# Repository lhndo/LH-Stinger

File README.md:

<p align="center">
  
	<h1 align="center"><b>LH Stinger</b></h1>
	<p align="center"> <strong>
		A no-compromise cartesian 3D Printer designed for speed and precision, created as a long-lasting platform for those who like to push quality and speed to the extreme.  </strong>
    <br />
    <br />
        <br />
    <i>~ A community-driven project ~ </i>
    <br /> 
    <br />
      
    <br />
</a>
  </p>
</p>

<br>

<br>

Status: **V1.0**  

<br>

## Sponsors

   Sponsored by [JLCPCB Flexible Heaters](https://flexheater.jlcpcb.com/?from=LH_STINGER) - **Custom Flex Heaters for Your Build**
<br>

## Contents

- [Features](#features)
- [Kits - BOM](#kits---bom)
- [Resources](#resources)
- [Assembly Instructions](#assembly-instructions)
- [Addons](#addons)
- [Contact](#contact)
- [Credits](#credits)
- [Supporters](#supporters)
- [License](#license)

<br>

## Features
_**(at BOM Spec)**_
<br>

- Cross Frame design focused on stiffness and stability with a low center of gravity
- Streamlined frame assembly consisting of only six extrusions
- Lightweight bed carriage assembly with carbon fiber components
- AWD stepper configuration for the Y-axis
  - Optional conversion for X-axis AWD setup
- 235 x 235 x 200 mm maximum build volume (easily expandable to other sizes)
  - (200 mm)^2 [Carbon Fiber Bed](/DXF) for high-speed setup
  - (235 mm)^2 bed support for a larger volume
- Optimized for daily print speeds of 400-600 mm/s with 20.000 mm/s^2 acceleration ([Test A](https://www.youtube.com/watch?v=bxNQv3xVFXA&)) ([Test B](https://www.youtube.com/watch?v=mh0rmYptH-0)) ([Test C](https://www.youtube.com/watch?v=cDipS-Msi5c))
- Motion system capable of 1.000 mm/s speed with 100.000 mm/s^2 acceleration ([Test](https://www.youtube.com/watch?v=Xajs2mky6ZU))
- Maximum volumetric flow rate: ~55-60 mm^3/s ([Test A](https://www.youtube.com/watch?v=K3M1EXKJzKs)) ([Test B](https://www.youtube.com/shorts/JorOoNuft90))
- Built using 30 series T-slotted extrusions with parts up to 3090
- All bracket assembly
- Genuine high-quality motion system components ([BOM](https://docs.google.com/spreadsheets/d/1s8ulLfThmbuy1G_40MvkXXL2oVx9PZhvpAY9hMxqYbg/edit?usp=drive_link))
- Entire motion system based on high preload MGN12H linear guide rails
- Fully belt-driven with minimal belt paths
- 9mm 2GT belt in symmetrical configuration for the Y-axis
- 6mm 2GT belts for the rest of the axis
- Independent Z stepper motors with Z Tilt capability for the X-axis
- Lightweight dual plate [Carbon Fiber Bed Carriage](/DXF) with integrated tensioner and compatible with different bed sizes and carriage configurations
- Rigid carbon fiber bed mount
- Lightweight Polyimide flex PCB 200W [Bed Heater](/PCB/PI%20Bed%20Heater%20-%20200mm)
- Double shear shaft supports for Y and X axis steppers
- High torque LDO-42STH48-2504AC stepper motors supplied with 36V for the X and Y-axis
- Dual power supply supporting 24V and 36V power standards (easily configurable for 48V)
- Driven by the Octopus Pro 1.1 board with TMC2240 drivers
- Running [Klipper](https://github.com/Klipper3d/klipper)/[Kalico](https://github.com/KalicoCrew/kalico) firmware
- Fully featured Klipper [Configuration](/Config/Klipper_Config) and [Slicer Profiles](/Config/Klipper_Config#slicers) available
- Easily serviceable [External electronic box](https://github.com/lhndo/LH-Stinger/wiki/Build-Log#electronic-box-design) with good airflow, and support for multiple power supplies, SSRs, RPi and large controller boards.
- Good cable management with a quick disconnect [Breakout Board](/PCB/LHS%20Breakbeat) between the printer and ebox
- Toolhead based on the Dragon HF hotend and HF extender
  - Alternate hotends supported: Dragon UHF, Ace, Mellow NF-Crazy-Volcano HF, Rapido, Goliath ([User Mods](/User_Mods/Toolhead/))
- LDO Orbiter 2.5 direct drive extruder
  - Sherpa Mini supported ([User Mods](/User_Mods/Printer))
- Dual 5015 fan setup for part cooling
- Dual [AUX cooling modules](/CAD/Aux%20Fan) based on 9733 blower fans providing 64 CFM of auxiliary cooling
- Adopts the [Annex Engineering Quickdraw Probe](https://github.com/Annex-Engineering/Quickdraw_Probe)
	- Zero Y offset probe placement for no gantry twist deviation
	- Full bed probe coverage
- Minimalistic [printed part design](/STL) focused on strength and easy printability
- Printed in ASA, providing high temperature resistance
- Easily enclosed, with the main electronic components outside of the build chamber.
  - The (200 mm)^2 bed configuration can be fully enclose up to the frame bounding box, with no extra space needed for the bed movement. ([Dimensions](https://github.com/lhndo/LH-Stinger/wiki/Dimensions))

<br>

**Resonance Tests:**<br>
<br>
<br>

<br>

## Kits - BOM

* This project can be self-sourced by following the [**BOM Guide**](https://docs.google.com/spreadsheets/d/1s8ulLfThmbuy1G_40MvkXXL2oVx9PZhvpAY9hMxqYbg/).  

* An official upgraded **LH Stinger - Rev2 Kit** is produced and sold by **[FYSETC](https://www.fysetc.com/products/lh-stinger-3d-printer-kit)**.

<br>

### Kit Highlights:

* Phaetus Dragon UHF - Hotend
* FYSETC Sherpa Mini - All Metal - CNC Extruder
* MGN 12H Z1 Preload Linear Rails
* FYSETC Spider V3.0 H7 (550Mhz) High Voltage board 
* 48V Power with TMC5160 Drivers (AWD Y, X Axis)
* High Torque 2.5A 580mN.m Stepper Motors with 30mm shafts for double shear support
* Delta (48V) and Meanwell (24V) PSUs
* Carbon Fiber Bed with Pre-applied PI Heater and Pre-epoxied CF Carriage Assembly
* LHS Breakbeat distribution board and wiring harness

**You require**: The **Printed Parts** and a **BTT Pi V1.2** or **Raspberry Pi** SBC (Klipper Host)
<br>

[**Fysetc - LH Stinger - Kit**](https://www.fysetc.com/products/lh-stinger-3d-printer-kit)  
  
Use the code **FYSBKSALELH** for a total of **$699**. Free shipping directly from US/EU.  
A portion of every kit sale goes towards supporting the project! :purple_heart:  

<br>

## Resources
<br>

- [**Assembly Guide**](https://github.com/lhndo/LH-Stinger/wiki/)
- [STL Files and Printing Instructions](STL/)  
- [CAD Source Files ](CAD/)
- [Klipper Configuration ](Config/Klipper_Config) 
- [Build Log](https://github.com/lhndo/LH-Stinger/wiki/Build-Log)
- [Videos](https://www.youtube.com/channel/UCPD2Ai4b49gVoCFSGFWoSdw) 

<br>

## Assembly Instructions 

* The [LH Stinger Wiki](https://github.com/lhndo/LH-Stinger/wiki) is a regularly updated and intended to serve as your primary point of reference during the build  

* The main body of documentation can be found in the [**Assembly Guide**](https://github.com/lhndo/LH-Stinger/wiki/Assembly-Guide)  

<br>

*For additional support please join us on the [LH Stinger Discord](https://discord.gg/EzssCfnEDS)*

<br>

## Addons

- [**LHS Pico MMU**](https://github.com/lhndo/LH-Stinger/wiki/Pico-MMU)  

- **Enclosure** *(In progress)* 
  *by zwirbel*

<br>

<br>

- An extensive range of [**community mods**]((/User_Mods)) available

<br>

## Contact

lemurshaze @ gmail.com  
@LH on [LH Stinger Discord](https://discord.gg/EzssCfnEDS)
<br>

## Credits

<br>

**Thanks to everyone in the LH Stinger community who supported the project, contributed in any form, or provided feedback! :purple_heart:**

<br>

_Inspired by the [Annex Engineering](https://github.com/Annex-Engineering) team and [community](https://discord.com/invite/MzTR3zE), along with the [Klipper community](https://discord.klipper3d.org), [RatRig](https://ratrig.com/) and all the crazy people that continue to push bed slingers to their limits. :purple_heart:_

-Toolhead evolved from an amazing design by [Dalegaard](https://github.com/dalegaard)  
-Silicon sock mold based on [Renátó Kulman](https://www.printables.com/@RenatoKulman)  
-Wago 221 mounts by [fns720](https://www.printables.com/@fns720)  
-SSR protection cover based on [Technoturk](https://www.printables.com/@Technoturk_377911)  
-3030 extrusion Cable clip based on [Arthur_C](https://www.printables.com/@Arthur_C_428094)  
-3030 t-nut clip based on [John_S](https://www.printables.com/@JohnS)  
<br>

## Supporters

<br>

*Special thanks to those who donated to this project throughout its development!* :purple_heart:  

**djezo888. Fen, Budz, techb0i, PinGZ, abstractFlo, BeccaK, Steven @crydteam, Robin @crydteam, Fred Bernton, Mawoka, rmxbit, Mcclane, malar6606, EMMY BEAR 3D, Killa_Prints, Michel, vr6deezy, Ajax240, Zemlos01, popster, Dan, Sibert, Ultracopa, yoske, Arjun, iKuro**  

If you would like to give your support, please use the link below:

<br>

## License

This work is licensed under a [Creative Commons (4.0 International License)  ](https://creativecommons.org/licenses/by-nc-sa/4.0/)  
[**Attribution—Noncommercial—Share Alike**](LICENSE.md)  

[![CC BY-NC-SA 4.0][cc-by-nc-sa-shield]][cc-by-nc-sa] [![DISCORD][s2]][l2] [![YOUTUBE][s5]][l5] 

[s1]: https://img.shields.io/badge/Buy%20Me%20a%20Coffeee-d3dsds?logo=ko-fi&logoColor=white&labelColor=red&color=red
[l1]: https://ko-fi.com/lh_eng
[s2]: https://img.shields.io/badge/Discord-asdsadsa?logo=discord&logoColor=white&color=5865F2
[l2]: https://discord.gg/EzssCfnEDS
[s5]: https://img.shields.io/badge/Youtube-8A2323443?logo=youtube&logoColor=red&color=white
[l5]: https://www.youtube.com/@LemurHaze

[cc-by-nc-sa]: http://creativecommons.org/licenses/by-nc-sa/4.0/
[cc-by-nc-sa-image]: https://licensebuttons.net/l/by-nc-sa/4.0/88x31.png
[cc-by-nc-sa-shield]: https://img.shields.io/badge/License-CC%20BY--NC--SA%204.0-lightgrey.svg

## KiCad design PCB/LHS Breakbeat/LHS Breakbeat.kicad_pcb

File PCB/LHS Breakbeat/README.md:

# LHS Breakbeat

- [LHS Breakbeat](#lhs-breakbeat)
  - [Features](#features)
  - [Specifications](#specifications)
  - [BOM](#bom)
  - [Notes](#notes)
- [Wiring Harness](#wiring-harness)
- [Guide](#guide)
- [Acknowledgments](#acknowledgments)

<br>

**Disclaimer**

>*This is a DIY (Do-It-Yourself) experimental project. This PCB is provided "as is" without any guarantees or warranty, and is not certified for any commercial or critical applications. Use it at your own risk. 
The creator assumes no liability for damages or injuries resulting from its use, including but not limited to fire, electric shock, personal injury or property damage.*
>*By using this PCB, you agree to the terms of this disclaimer.*

<br>

**NOTE: this design is currently in testing**  

<br>

**LHS Breakbeat** is a breakout board built for the LH Stinger, meant to provide an easy interface between the external electronics box and the printer electronics.

This board is meant to be mounted on the printer, and make most of the wiring setup plug and play.

## Features
* Support for 7 stepper motors
* 3 Thermistors
* 3 Fans with individual power requirements
  * 4-pin fan support
* 4 Endstops
* RGB lighting
* Optional probe header
* Filament Sensor (Tach and F Sens pins are shared)
* Fused bed and hotend power lines 
* Support for separate thermistor analog ground
* CAN bus alternative wiring
* Thermistor test points
* Tachometer diode protection

<br>

## Specifications

Note: these guideline limits are on top of your mainboard specifications, along with the wires and connectors used for the wire harness.

Circuit | Limit
--|--
Hotend Heater | 24V, 115W, 4.8 A 
Bed Heater | 24V, 220W, 9.2 A
Fans | 24V, 2 A 
RGB/5V | 2A
Steppers | 2.7 A

## BOM
Please see the [Interactive BOM](https://htmlpreview.github.io/?https://github.com/lhndo/LH-Stinger/blob/main/PCB/LHS%20Breakbeat/BOM/ibom.html)

## Notes

* The BOM included links to paired connectors and crimps
* The Molex MiniFit Paired Power Connector (03-04-4052) requires 16AWG 13A crimps (45750-3112)

<br>

# Wiring Harness

<br>

# Guide

https://github.com/lhndo/LH-Stinger/wiki/Breakout-Box

# Acknowledgments

*Thanks to [@roerich_64](https://github.com/walterwissmann) and the LHS community for the help and guidance with this project!*

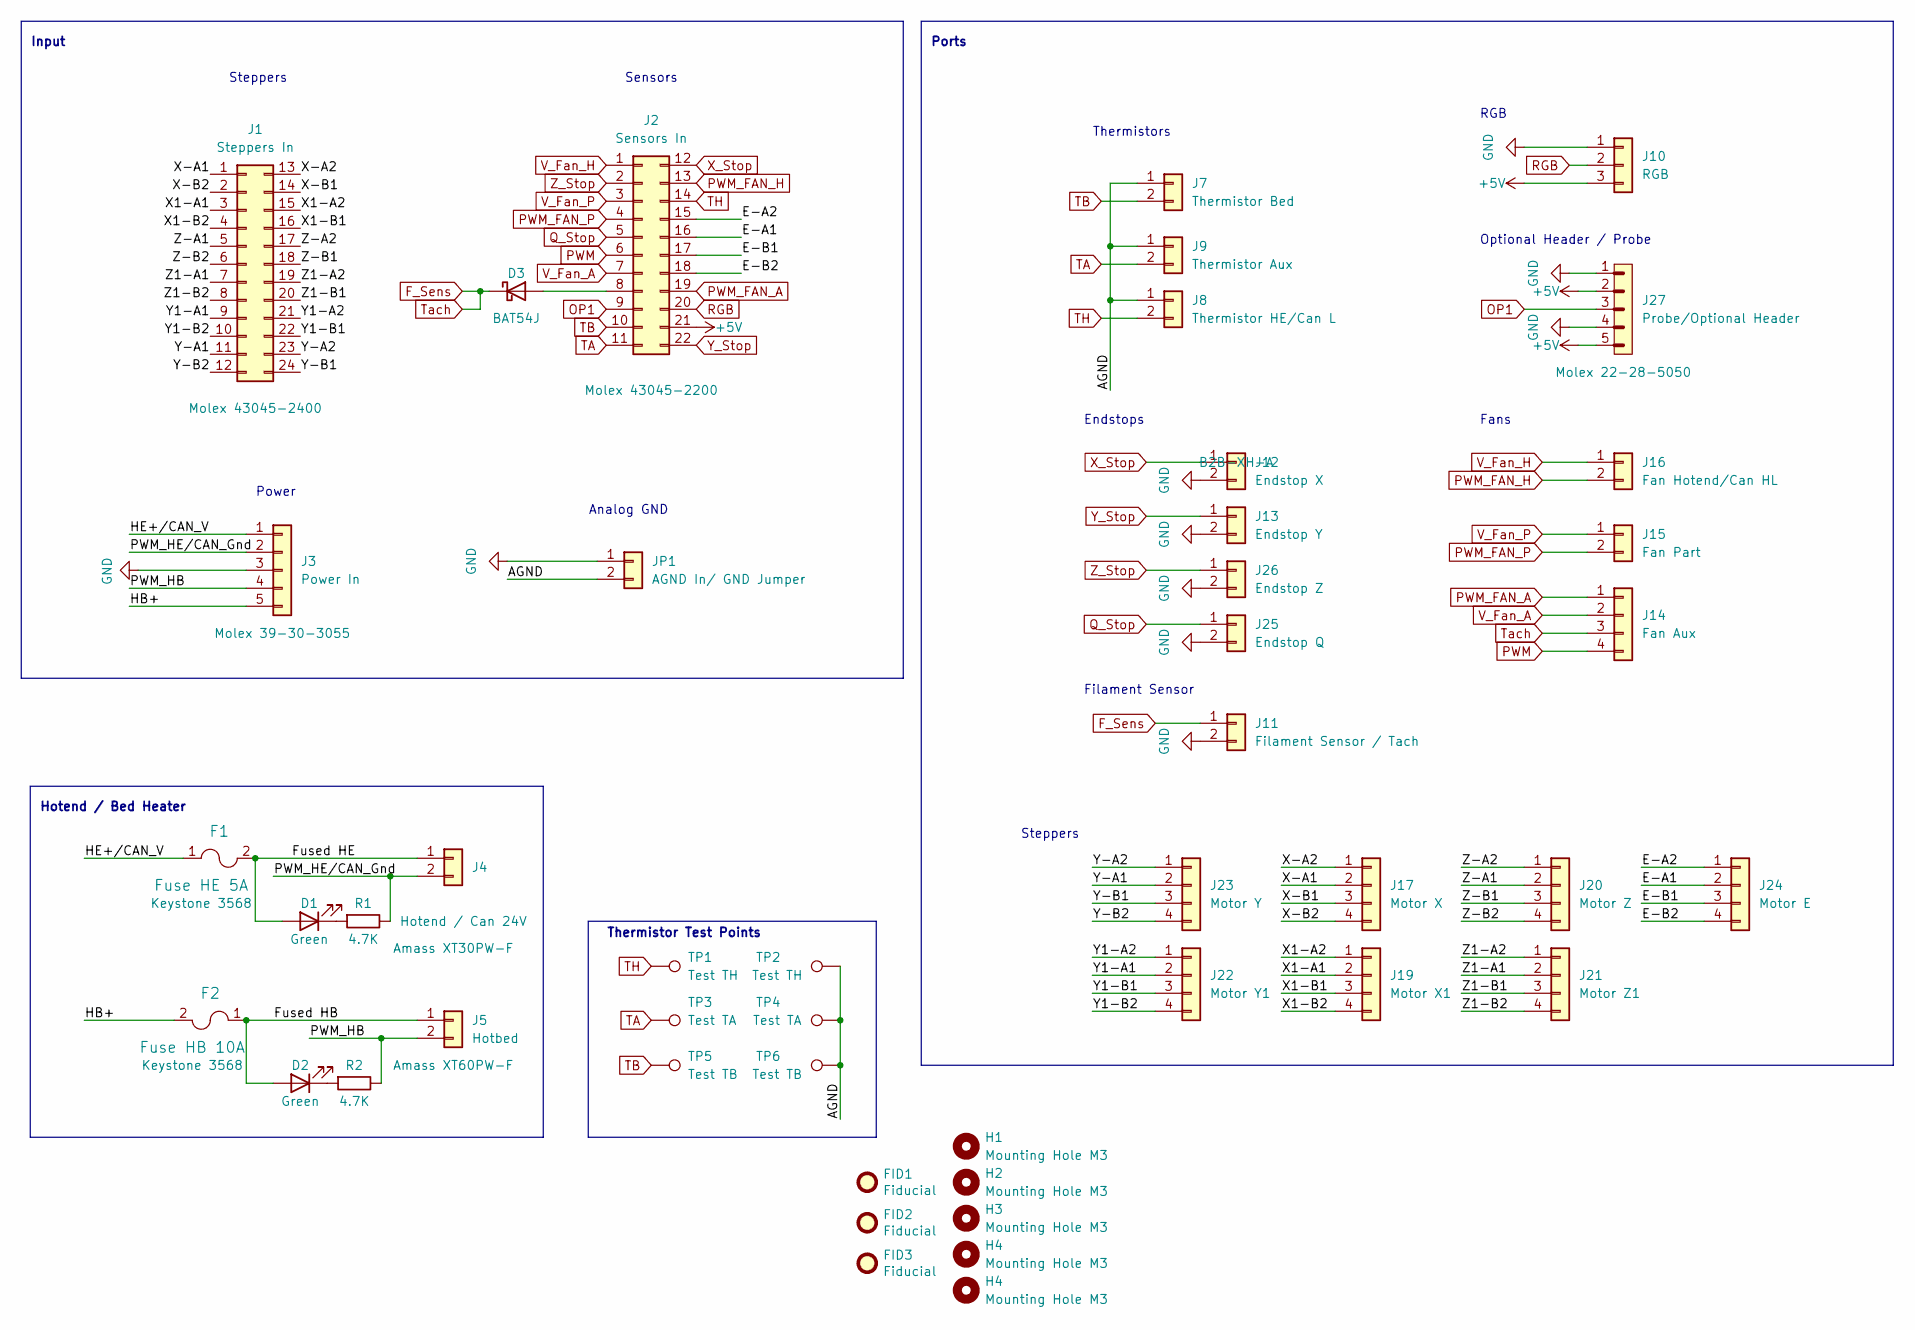
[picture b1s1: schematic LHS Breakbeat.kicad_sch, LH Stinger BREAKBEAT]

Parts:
D1, D2: Green; LED_0805_2012Metric_Pad1.15x1.40mm_HandSolder; LCSC C2297
D3: BAT54J; D_SOD-323F; LCSC C130415
F1: Fuse HE 5A; Fuseholder_Blade_Mini_Keystone_3568; LCSC C3206956
F2: Fuse HB 10A; Fuseholder_Blade_Mini_Keystone_3568; LCSC C3206956
FID1, FID2, FID3: Fiducial; Fiducial_1.5mm_Mask3mm
H1, H2, H3, H4: Mounting Hole M3; MountingHole_3.2mm_M3_DIN965_Pad
J1: Steppers In; 0430452400; LCSC C277384
J2: Sensors In; 43045-22_00,01,02,10_; LCSC C127339
J3: Power In; 39303055; LCSC C485326
J4: Hotend / Can 24V; XT30PWF; LCSC C2913282
J5: Hotbed; AMASS_XT60PW-F_1x02_P7.20mm_Horizontal; LCSC C428722
J7: Thermistor Bed; JST_XH_B2B-XH-A_1x02_P2.50mm_Vertical; LCSC C5258883
J8: Thermistor HE/Can L; JST_XH_B2B-XH-A_1x02_P2.50mm_Vertical; LCSC C5258883
J9: Thermistor Aux; JST_XH_B2B-XH-A_1x02_P2.50mm_Vertical; LCSC C5258883
J10: RGB; JST_XH_B3B-XH-A_1x03_P2.50mm_Vertical; LCSC C492457
J11: Filament Sensor / Tach; JST_XH_B2B-XH-A_1x02_P2.50mm_Vertical; LCSC C5258883
J12: Endstop X; JST_XH_B2B-XH-A_1x02_P2.50mm_Vertical; LCSC C5258883
J13: Endstop Y; JST_XH_B2B-XH-A_1x02_P2.50mm_Vertical; LCSC C5258883
J14: Fan Aux; JST_XH_B4B-XH-A_1x04_P2.50mm_Vertical; LCSC C709375
J15: Fan Part; JST_XH_B2B-XH-A_1x02_P2.50mm_Vertical; LCSC C5258883
J16: Fan Hotend/Can HL; JST_XH_B2B-XH-A_1x02_P2.50mm_Vertical; LCSC C5258883
J17: Motor X; JST_XH_B4B-XH-A_1x04_P2.50mm_Vertical; LCSC C709375
J19: Motor X1; JST_XH_B4B-XH-A_1x04_P2.50mm_Vertical; LCSC C709375
J20: Motor Z; JST_XH_B4B-XH-A_1x04_P2.50mm_Vertical; LCSC C709375
J21: Motor Z1; JST_XH_B4B-XH-A_1x04_P2.50mm_Vertical; LCSC C709375
J22: Motor Y1; JST_XH_B4B-XH-A_1x04_P2.50mm_Vertical; LCSC C709375
J23: Motor Y; JST_XH_B4B-XH-A_1x04_P2.50mm_Vertical; LCSC C709375
J24: Motor E; JST_XH_B4B-XH-A_1x04_P2.50mm_Vertical; LCSC C709375
J25: Endstop Q; JST_XH_B2B-XH-A_1x02_P2.50mm_Vertical; LCSC C5258883
J26: Endstop Z; JST_XH_B2B-XH-A_1x02_P2.50mm_Vertical; LCSC C5258883
J27: Probe/Optional Header; PinHeader_1x05_P2.54mm_Vertical; LCSC C2935911
JP1: AGND In/ GND Jumper; PinHeader_1x02_P2.54mm_Vertical; LCSC C2685195
R1, R2: 4.7K; R_0805_2012Metric_Pad1.20x1.40mm_HandSolder; LCSC C17673
TP1, TP2: Test TH; TestPoint_Pad_D2.0mm
TP3, TP4: Test TA; TestPoint_Pad_D2.0mm
TP5, TP6: Test TB; TestPoint_Pad_D2.0mm

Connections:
+5V: J2.21, J10.3, J27.2, J27.5
/AGND: J7.1, J8.1, J9.1, JP1.2, TP2.1, TP4.1, TP6.1
/E-A1: J2.16, J24.2
/E-A2: J2.15, J24.1
/E-B1: J2.17, J24.3
/E-B2: J2.18, J24.4
/Fused HB: D2.2 (A), F2.1, J5.1
/Fused HE: D1.2 (A), F1.2, J4.1
/HB+: F2.2, J3.5
/HE+/CAN_V: F1.1, J3.1
/PWM_HB: J3.4, J5.2, R2.2
/PWM_HE/CAN_Gnd: J3.2, J4.2, R1.2
/X1-A1: J1.3, J19.2
/X1-A2: J1.15, J19.1
/X1-B1: J1.16, J19.3
/X1-B2: J1.4, J19.4
/X-A1: J1.1, J17.2
/X-A2: J1.13, J17.1
/X-B1: J1.14, J17.3
/X-B2: J1.2, J17.4
/Y1-A1: J1.9, J22.2
/Y1-A2: J1.21, J22.1
/Y1-B1: J1.22, J22.3
/Y1-B2: J1.10, J22.4
/Y-A1: J1.11, J23.2
/Y-A2: J1.23, J23.1
/Y-B1: J1.24, J23.3
/Y-B2: J1.12, J23.4
/Z1-A1: J1.7, J21.2
/Z1-A2: J1.19, J21.1
/Z1-B1: J1.20, J21.3
/Z1-B2: J1.8, J21.4
/Z-A1: J1.5, J20.2
/Z-A2: J1.17, J20.1
/Z-B1: J1.18, J20.3
/Z-B2: J1.6, J20.4
F_Sens: D3.1 (K), J11.1, J14.3
GND: J3.3, J10.1, J11.2, J12.2, J13.2, J25.2, J26.2, J27.1, J27.4, JP1.1
unnamed: D1.1 (K), R1.1
unnamed: D2.1 (K), R2.1
unnamed: D3.2 (A), J2.8
OP1: J2.9, J27.3
PWM: J2.6, J14.4
PWM_FAN_A: J2.19, J14.1
PWM_FAN_H: J2.13, J16.2
PWM_FAN_P: J2.4, J15.2
Q_Stop: J2.5, J25.1
RGB: J2.20, J10.2
TA: J2.11, J9.2, TP3.1
TB: J2.10, J7.2, TP5.1
TH: J2.14, J8.2, TP1.1
V_Fan_A: J2.7, J14.2
V_Fan_H: J2.1, J16.1
V_Fan_P: J2.3, J15.1
X_Stop: J2.12, J12.1
Y_Stop: J2.22, J13.1
Z_Stop: J2.2, J26.1

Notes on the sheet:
Fans
Analog GND
Power
Endstops
Input
Hotend / Bed Heater
Steppers
Ports
Thermistors
Optional Header / Probe
Filament Sensor
Thermistor Test Points
Sensors
RGB

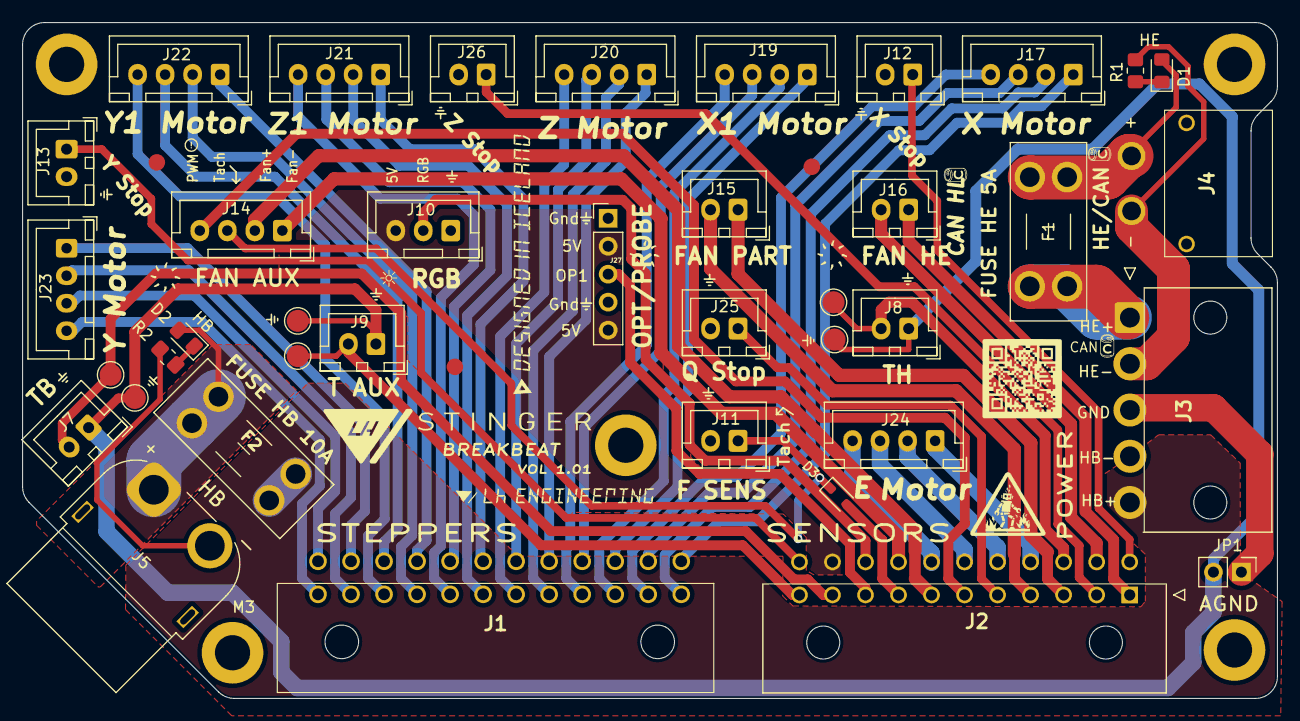
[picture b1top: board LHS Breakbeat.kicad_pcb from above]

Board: 2 copper layers, 114.0 x 61.4 mm, 47 parts (0 on the bottom side), 57 nets.

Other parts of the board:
H5: Mounting Hole M3; MountingHole_3.2mm_M3_DIN965_Pad

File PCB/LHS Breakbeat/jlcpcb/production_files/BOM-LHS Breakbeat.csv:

Comment,Designator,Footprint,LCSC
Sensors In,J2,"43045-22_00,01,02,10_",C127339
BAT54J,D3,D_SOD-323F,C130415
4.7K,"R1,R2",R_0805_2012Metric_Pad1.20x1.40mm_HandSolder,C17673
Green,"D1,D2",LED_0805_2012Metric_Pad1.15x1.40mm_HandSolder,C2297
AGND In/ GND Jumper,JP1,PinHeader_1x02_P2.54mm_Vertical,C2685195
Steppers In,J1,0430452400,C277384
Hotend / Can 24V,J4,XT30PWF,C2913282
Probe/Optional Header,J27,PinHeader_1x05_P2.54mm_Vertical,C2935911
Fuse HE 5A,"F1,F2",Fuseholder_Blade_Mini_Keystone_3568,C3206956
Hotbed,J5,AMASS_XT60PW-F_1x02_P7.20mm_Horizontal,C428722
Power In,J3,39303055,C492364
RGB,J10,JST_XH_B3B-XH-A_1x03_P2.50mm_Vertical,C492457
Filament Sensor / Tach,"J11,J12,J13,J15,J16,J25,J26,J7,J8,J9",JST_XH_B2B-XH-A_1x02_P2.50mm_Vertical,C5258883
Fan Aux,"J14,J17,J19,J20,J21,J22,J23,J24",JST_XH_B4B-XH-A_1x04_P2.50mm_Vertical,C709375

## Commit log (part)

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2024-08-22 explicitly defining extruder speed limits due to possibly wrong klipper default value calculations
2024-08-24 adding fluidd theme
2024-08-25 adding micro cuts to X Endstop to help with bridging layer
2024-08-25 increasing the tolerance of the X Toolhead Tensioner block
2024-08-26 updating zone names
2024-08-30 adding information and linking to the wiki mod guide
2024-09-01 decreasing bottom part thickness to increase clearance against Y extrusion
2024-09-02 updating setup instruction
2024-09-02 updating bed PID and sensor values
2024-09-04 updating hz_per_sec to speed up testing
2024-09-04 adding a custom TPOWERDOWN setting of ~4.3 seconds along with 1A hold current for the HV steppers
2024-09-05 adding max_extrude_cross_section as a safety measure for purges
2024-09-05 enabling [resonance_holder] by default and adding documentation links
2024-09-05 Resonance Holder now part of the main configuration
2024-09-06 improving AWD sync and FORCE_SET_POS to lock at full steps, prefixing NON-UI macros to for exclusion (_PURGE_LINE, _GO_....)
2024-09-09 renaming folder
2024-09-10 updating Z right drive to universal bearing clamp version
2024-09-10 setting speeds for FORCE_UP DOWN macros
2024-09-15 marking the bed heater alignment guide plate as "not for fysetc"
2024-09-15 lowering nozzle pre-heat target to prevent oozing
2024-09-17 updating header FW flashing instructions
2024-09-21 updating formatting
2024-09-21 adding wiring diagram
2024-09-22 adding UL3239 to power wiring specifications
2024-09-25 fixing typo in max_extrude_cross value
2024-09-25 changing 5160 stepper drivers to hardware spi
2024-09-29 adding TPU profiles
2024-10-03 print start: adding an extra Z home just before docking
2024-10-08 adding Stinger Pico MU - prototype
2024-10-09 Updating UL codes
2024-10-09 updating BOM
2024-10-11 adding Pico MMU step file
2024-10-15 Pico MMU: adding optional ECAS fittings
2024-10-16 disabling my_end_retract moves if the value is set to 0
2024-10-20 adding other parts - accesories - for the Pico MMU
2024-10-22 integrated cam shaft update
2024-10-22 updating ResHelper instructions and simplifying intallation steps
2024-10-24 taller roller rims and concave profile, adding attachment slot to mid section for future accesories
2024-10-26 adding Pico MMU documentation link
2024-10-27 adding note regarding park at cancel
2024-10-27 adding Stinger Pico MMU Klipper code
2024-10-28 fixed screw quantities
2024-10-28 fixing version check
2024-11-23 Increrasing tolerances of the Cable Clamps
2024-11-27 decreasing tolerances for the X inner tensioner piece for ease of installation
2024-12-02 updated heatbed instructions
2024-12-02 adding other platforms paths
2024-12-03 moving stl files
2024-12-03 adding heat insert for the left fan arm on sherpa variants
2024-12-03 updating UHF toolhead variant for left fan heat insert
2024-12-06 fixing title
2024-12-06 adding download folder link
2024-12-06 added bom links
2024-12-06 renaming Other Parts to Accessories
2024-12-07 removing dock adjustment note
2024-12-07 fixing SP_TEST_MMU
2024-12-07 updating plates image preview
2024-12-07 updating adxl configs for the new sweeping vibrations resonance testing
2024-12-09 fixing end_of_load_filament_move
2024-12-09 adding accel per hz recommendation
2024-12-09 adding restart method to serial connection
2024-12-11 adding 4 lane version
2024-12-11 updating Pico MMU hardware configuration example
2024-12-11 added print plates thumbnail
2024-12-12 adding long shaft link
2024-12-13 adding automatic "Quiet" profile detection part of print start
2024-12-14 setting first layer to rectilinear, adding brim and removing el foot compensation for better overhang fillets
2024-12-15 updating servo link
2024-12-17 updated code and configuration to v0.4 added support for different hub configurations fine tuned movement stages for non ideal setups various other fixes and improvements
2024-12-17 increasing default servo switch time for safety
2024-12-17 adding part variants with higher tolerances - marked with a dot
2024-12-18 adding RatOS T0 conflict workaround
2024-12-19 updating load/unload macros to retain the target heat when ran by default
2024-12-19 tweaking default lengths, bringing synced move closer to sensor and reverting tip forming initial move from 1mm to 0.5mm
2024-12-21 updating Fysetc Spider H7 Mount
2024-12-23 updated print settings and bom
2024-12-23 removing 4 lane section
2024-12-23 specifying tpu, rubber or silicon patch thickness
2024-12-25 painted seams
2024-12-26 update to 0.5 - refactoring and simplifying moves - implementing home_before_downchange - adding simulated pause retract on unload lane - defaulting to loaded lane on unload macros
2024-12-27 updating mainsail and fluidd configs to include the MANUAL TIP FORMING TEST macro
2024-12-28 reverting to 2 wall perimeters
2025-01-02 fixing park command
2025-01-04 udpated base plate channels for easier faliment loading
2025-01-05 fixing Z restore position
2025-01-07 updating part tolerances around the microswitch
2025-01-09 adding Belt Drive version
2025-01-11 Toolhead for Teakettle
    Toolhead for Teakettle
2025-01-14 updating tie bars, idler arms, cam shaft spacers
2025-01-15 adding BTT Pi power relay setup info
2025-01-17 refactoring hotend heating
2025-01-18 lowering the hotend loading speed for the final stage aproaching the meltzone
2025-01-19 removing detract before resume
2025-01-21 enforcing lost classic perimeters, adding single perimeter on tops, changing mmu purge tower settings, adding mmu print profile, adding purge volume set macro to the printer mmu profile
2025-01-24 updating configuration scripts to automate the klipper config setup procedure
2025-01-24 changing header
2025-01-24 Second _SP_TEST is empty can causes a non-reponse
2025-01-25 added comment regarding runout pause
2025-01-26 lowering homing speed to avoid loud motor resonances
2025-01-27 adding Brush Purge Dock
2025-01-27 removed tpu tab mention
2025-01-29 updating mmu settings
2025-01-29 updating user macro execution messages
2025-01-30 adding Filament Cutters by RPi
2025-01-30 tweaking bom notes
2025-01-31 lowering minimum safety temp to 180
2025-01-31 trying workaround for timer too close issue https://klipper.discourse.group/t/mcu-mmboard-shutdown-timer-too-close/376/2
2025-02-04 increasing the default cooldown dist (5 to 20) for hotends prone to heatcreep
2025-02-06 turning off hotend after change at print start
2025-02-07 adding flip stop cut
2025-02-07 adding optional heat range setting for head and wait commands
2025-02-07 updating documentation
2025-02-09 updating jig stl
2025-02-09 chaging default Y position while waiting for hotent heating to avoid the bed sitting over the motor mounts
2025-02-09 resetting filament settings
2025-02-13 assuming hotend loaded during init filament state mismatch
2025-02-13 trying to catch SAVE_VARIABLE config issues
2025-02-13 adding grams of filament required
2025-02-14 adding notes regarding using spare mainboards and asking the community for hub solutions
2025-02-16 rename
2025-02-20 - Adding REFRESH_STATE calls thoughout the manual macros to obtain fresh sensor state - Adding NO_START_PURGE option to _SP_PRINT_START for custom purge setups - Disabling RESTORE_PA from triggering 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
2025-02-21 setting next purge to 0 when no filament change is required during sp print start
2025-02-21 adding print_start_change variable which tracks if a filament change was required at print start
2025-02-23 fixing Top A orientation
2025-02-24 adding image
2025-02-26 fixing purging during infinite spool, adding messaging regarding purge amount
2025-02-26 adding a convenience 0.25 vase mode profile - requires decreasing filament min layer time to ~2s
2025-02-28 adding ECAS floating Hub variants
2025-03-02 specifying hardened drive gears and pairs qty
2025-03-03 adding CNC Sherpa mini - Filament Hub Holder - by RPi
2025-03-04 chaging default end retract to 1mm
2025-03-05 implementing soft heat and wait targets for hotend heating
2025-03-05 adding hotend off message during print start
2025-03-05 adding purge temperature management example
2025-03-07 inverting Z direction pins
2025-03-07 changing macro parameters types
2025-03-07 changing other macro parameter types
2025-03-07 defaulting config to 4 lanes
2025-03-09 fixing params logic in manual macro and enforcing params type casting
2025-03-12 fixing filament change error when unload lane is empty
2025-03-19 changing switch to GM 8.0
2025-03-24 - changing saved variable detection at boot for better behaviour when config not preset - fixing SP_FORCE_SET_LOADED_LANE hotend loaded variable - adding support for Kalico non linear pressure advanc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
2025-03-25 adding annotations
2025-03-31 removing pause from the z-offset warning
2025-04-01 taking Z homing origin into account when calculating Z safety margin @khoanguyen and chaging saved variables for X, Y to gcode position instead of toolhead
2025-04-03 reverting tip forming cooldown distance to 5mm and lowering meltzone loading speed to 10mm/s
2025-04-03 fixing retract move for legacy sync method
2025-04-05 adding more G4 and M400 guards
2025-04-25 mentioning round shaft alt mod
2025-05-06 adding dummy dwell for people with soft filament in extruder issues
2025-05-29 Adding PCTG profile Adding commented parameters for filament G-Code related to Kalico/MPC/NA PA Refining PETG print profile Increasing overall first layer speeds Fine tuning support settings
2025-06-02 Update configuration template version to 0.9.2. Introduced _SP_PURGE user macro which is called whenever a purging action is performed. Performs conditional homing when paraking is enabled.
2025-06-03 cleanup
2025-06-03 adding skip_first_park advance option - 1/0 - disable the first parking move when using filament cutters which take over that task
2025-06-04 Tweaks
2025-06-08 adding initial park move
2025-06-08 fixing speed variable and adding Y move
2025-06-08 adding extra blade from Mawoka
2025-06-08 adding short action stopper
2025-06-19 Updating X tensioner block to avoid layer separation on block insertion
2025-06-25 updating Orca build plate image
2025-07-14 adding cron / background services setup instructions
2025-07-18 Disabled thick internal bridges First layer perimeters lowered from 90 to 60 Decreased PLA min layer time to 8 and increased min speed to 15 Enabled Slow down for curled perimeters Removed optinal no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
2025-07-18 Updating X Bearing Insert part for better fit
2025-07-24 adding filament cutter stopper placement instructions
2025-07-24 small tweaks
2025-07-30 disable runout on pico disable
2025-08-15 adding gcode-shell-command module installation
2025-08-17 removing unnecessary initial servo angle setup
2025-08-19 Increasing tolerances to aid easier hotend insertion and updating instructions
2025-08-21 adding Goliath Sherpa Mini variant and updating instructions
2025-08-21 adding Chube - 2510 Fan Flow guide - untested
2025-08-30 Adding Orbiter - Flipped direction cutter body
2025-09-05 changing description of variable_legacy_klipper
2025-09-05 adding Pico MMU configuration for LH Stinger - Fysetc Kit
2025-09-08 tweaking SP_TEST_SYNC printout message
2025-09-14 Including negative cutout shape
2025-09-30 Chaging default to variable_legacy_klipper: 1 due to latest klipper issues. Should help people on first set-up
2025-10-09 tweaking SP_SYNC_TEST printout
2025-12-02 syncing CAD with latest
2025-12-14 restoring velocity limits before resuming print
2025-12-18 tweaking rear wiring tolerances - @Wight554
2026-01-03 Introduced sync_mode variable and deprecated legacy klipper mode Configuration template upgraded to 0.9.3
    sync_mode = 2 < Klipper Latest
    sync_mode = 1 < Klipper Old
    sync_mode = 0 < Klipper v0.12.0 - v0.13.0 or Kalico
    test with: SP_TEST_SYNC SYNC_MODE=0 .. [0..2]
    Migrate instructions:
    - update sp_mmu_code.cfg
2026-01-06 updated notes
2026-02-25 adding two part variants recommendation
2026-03-13 Fix STOP_ON_ENDSTOP deprecated warning
2026-04-14 updating configuration templates to 0.94 enabling guest lane by default
2026-05-26 Tweaks and brim
2026-06-26 Updating Orca Slicer profile info
